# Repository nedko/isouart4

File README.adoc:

:notitle:
:keywords: isouart4
:docinfo: private-head,private-header

= isouart4 - Galvanically Isolated USB attached Quad UART

isouart4 - OSHW Galvanically Isolated USB attached Quad UART

.WORK IN PROGRESS
[NOTE]
This is Work In Progress.

link:bom/ibom.html[BOM - Bill Of Materials]

link:isouart4_sch.pdf[Schematic PDF]

link:https://gitea.ladish.org/nedko/isouart4[Project files] for link:https://kicad.org/[KiCAD]

image:isouart4-bottom.jpg[PCB bottom]

image:isouart4-top.jpg[PCB top]

== See also

 * link:https://github.com/hexeguitar/4WD_UART[4WD_UART by Piotr Zapart] is similar project that heavily influenced isouart4 design

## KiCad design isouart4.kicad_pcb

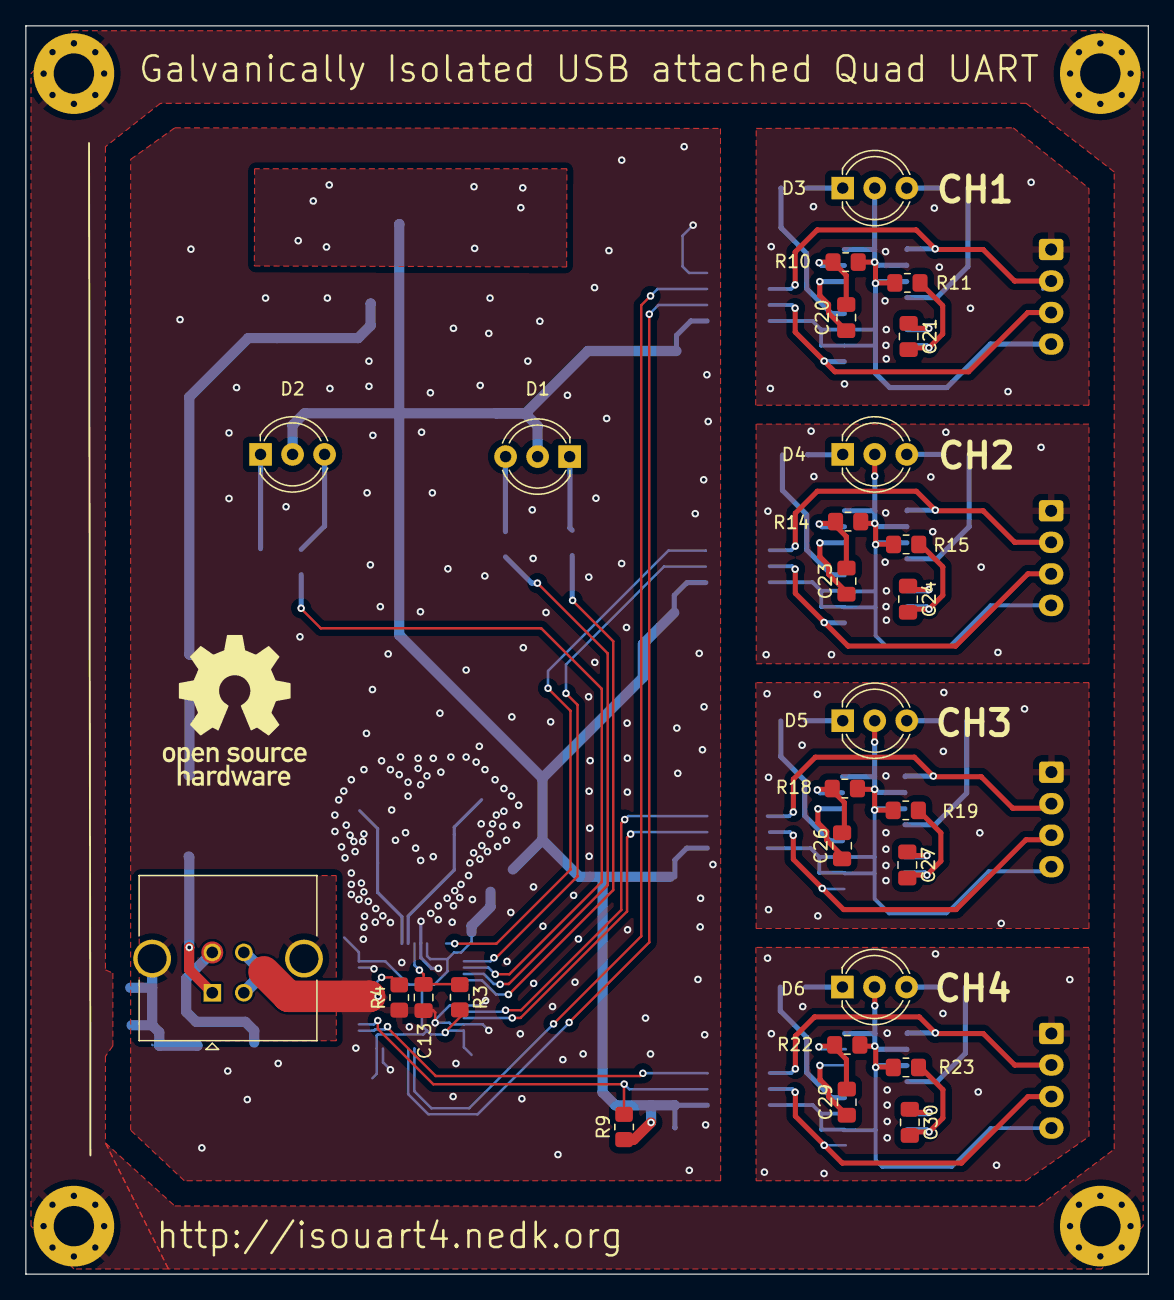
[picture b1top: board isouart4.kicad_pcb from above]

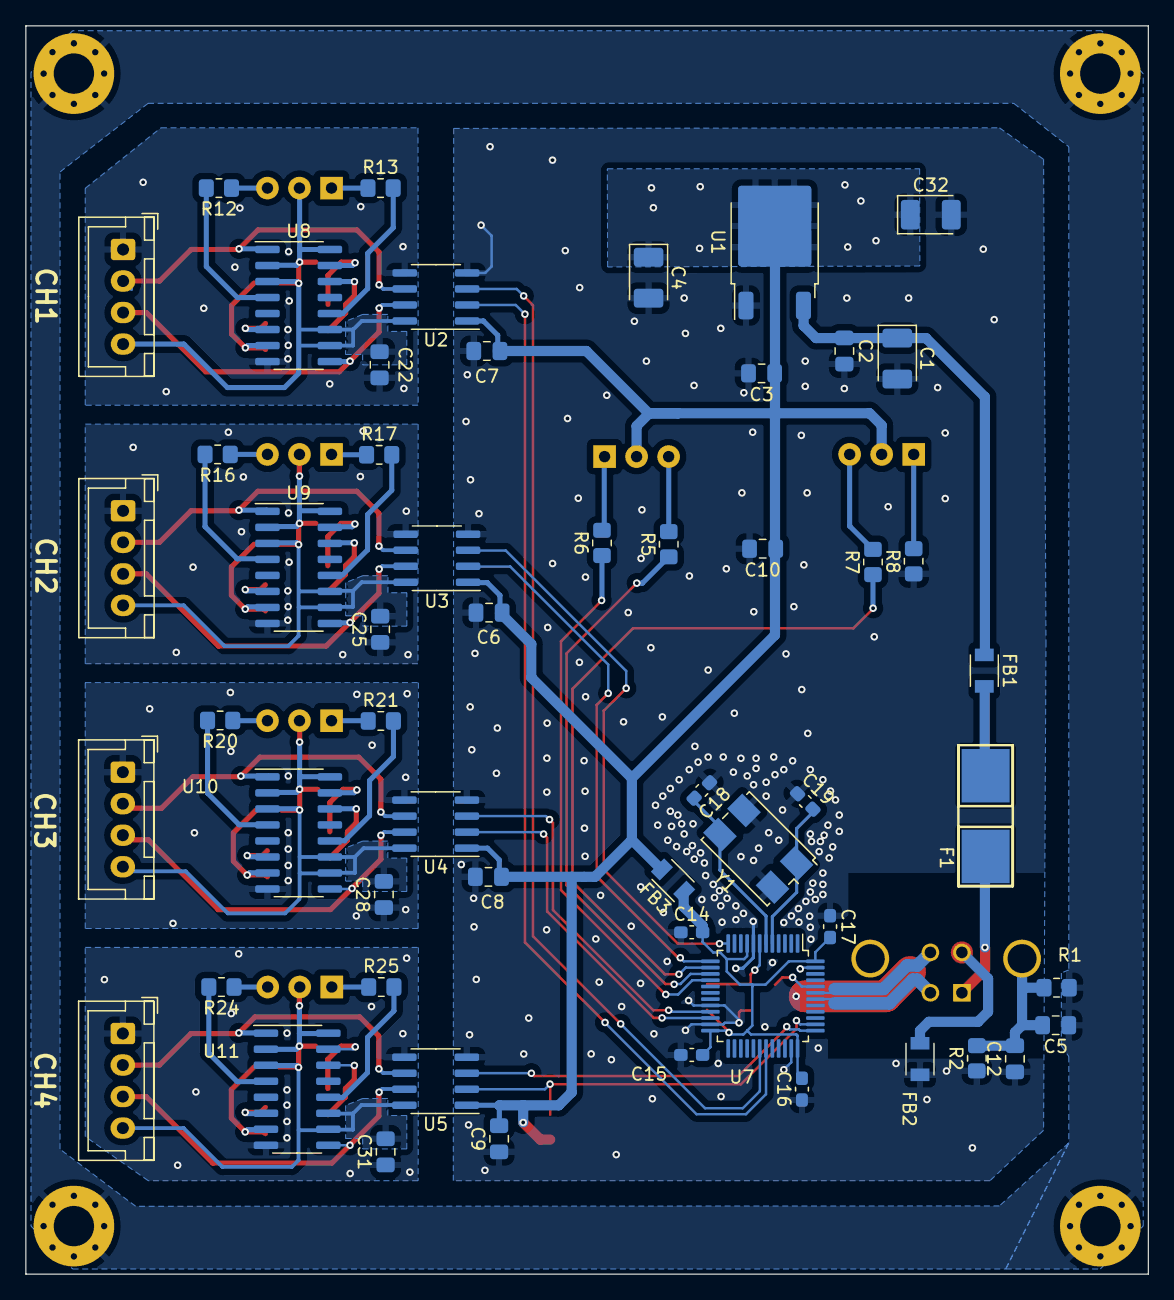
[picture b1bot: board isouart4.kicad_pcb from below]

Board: 2 copper layers, 89.0 x 99.0 mm, 87 parts (55 on the bottom side), 78 nets.

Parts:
C1, C4, C32: 2.2uF; CP_EIA-3528-15_AVX-H_Pad1.50x2.35mm_HandSolder
C2, C3, C6, C7, C8, C9, C10, C13, C22, C25, C28, C31: 100n; C_0805_2012Metric_Pad1.18x1.45mm_HandSolder
C5, C12: 4n7; C_0805_2012Metric_Pad1.18x1.45mm_HandSolder
C14, C15, C16, C17: 100n; C_0603_1608Metric_Pad1.08x0.95mm_HandSolder
C18, C19: 22p; C_0603_1608Metric_Pad1.08x0.95mm_HandSolder
C20, C21, C23, C24, C26, C27, C29, C30: 1uF; C_0805_2012Metric_Pad1.18x1.45mm_HandSolder
D1, D2, D3, D4, D5, D6: LED_Dual_KAK; LED_D5.0mm-3
F1: 100mA; FuseX
FB1, FB2, FB3: 100R; FB_0805_2012Metric
H1, H2, H3, H4: MountingHole; MountingHole_3.2mm_M3_Pad_Via
J1: USB_B; USB_B_TE_5787834_Vertical
J2, J3, J4, J5: Conn_01x04; JST_XH_B4B-XH-A_1x04_P2.50mm_Vertical
LOGO1: OSHW
R1: 4K7; R_0805_2012Metric_Pad1.20x1.40mm_HandSolder
R2: 1M; R_0805_2012Metric_Pad1.20x1.40mm_HandSolder
R3, R4, R9: 4k7; R_0805_2012Metric_Pad1.20x1.40mm_HandSolder
R5, R6, R7, R8, R12, R13, R16, R17, R20, R21, R24, R25: 1k; R_0805_2012Metric_Pad1.20x1.40mm_HandSolder
R10, R11, R14, R15, R18, R19, R22, R23: 220k; R_0805_2012Metric_Pad1.20x1.40mm_HandSolder
U1: LP2950CDT-3.3; TO-252-2
U2, U3, U4, U5: π122U31; SOIC-8_3.9x4.9mm_P1.27mm
U7: CH344Q; LQFP-48_7x7mm_P0.5mm
U8, U9, U10, U11: 74HC123; SOIC-16_3.9x9.9mm_P1.27mm
Y1: 8MHz; Crystal_SMD_7050-4Pin_7.0x5.0mm

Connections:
/GNDUSBCONN: FB2.1, J1.4 (GND)
/SHLD: C5.1, H1.1, H2.1, H3.1, H4.1, R1.1
/USB-UART4-CH344Q/ACT: R7.1, U7.14 (ACT|CFG|DCD3)
/USB-UART4-CH344Q/D+: J1.3 (D+), U7.43 (UD+)
/USB-UART4-CH344Q/D-: J1.2 (D-), U7.42 (UD-)
/USB-UART4-CH344Q/RESET: C13.2, R3.1, U7.7 (RESET)
/USB-UART4-CH344Q/RX1: U2.2 (VOA), U7.31 (RXD0)
/USB-UART4-CH344Q/RX2: U3.2 (VOA), U7.13 (RXD1)
/USB-UART4-CH344Q/RX3: U4.2 (VOA), U7.22 (RXD2)
/USB-UART4-CH344Q/RX4: R9.2, U5.2 (VOA), U7.38 (RXD3)
/USB-UART4-CH344Q/RX_S: R6.1, U7.16 (RX_S|DSR3)
/USB-UART4-CH344Q/TEST: R4.2, U7.44 (TEST)
/USB-UART4-CH344Q/TX1: U2.3 (VIB), U7.30 (TXD0)
/USB-UART4-CH344Q/TX2: U3.3 (VIB), U7.12 (TXD1)
/USB-UART4-CH344Q/TX3: U4.3 (VIB), U7.21 (TXD2)
/USB-UART4-CH344Q/TX4: U5.3 (VIB), U7.37 (TXD3)
/USB-UART4-CH344Q/TX_S: R5.1, U7.15 (TX_S|RI3)
/USB-UART4-CH344Q/VIN 3.3V: C3.1, C4.1, C6.2, C7.2, C8.2, C9.2, C10.1, C32.1, D1.2 (A), D2.2 (A), FB3.2, R9.1, U1.2 (VO), U2.1 (VDD1), U3.1 (VDD1), U4.1 (VDD1), U5.1 (VDD1)
/USB-UART4-CH344Q/XI: C19.2, U7.5 (XI), Y1.1
/USB-UART4-CH344Q/XO: C18.2, U7.6 (XO), Y1.3
/USBSHLD: C5.2, C12.2, J1.5 (Shield), R1.2, R2.2
/indicators-ch1/GNDMON: C22.1, J2.1, U2.5 (GND2), U8.8 (GND)
/indicators-ch1/RXMON: J2.3, U2.7 (VIA), U8.9 (A)
/indicators-ch1/TXMON: J2.2, U2.6 (VOB), U8.1 (A)
/indicators-ch1/V+MON: C22.2, D3.2 (A), J2.4, R10.1, R11.1, U2.8 (VDD2), U8.2 (B), U8.3 (Clr), U8.10 (B), U8.11 (Clr), U8.16 (VCC)
/indicators-ch2/GNDMON: C25.1, J3.1, U3.5 (GND2), U9.8 (GND)
/indicators-ch2/RXMON: J3.3, U3.7 (VIA), U9.9 (A)
/indicators-ch2/TXMON: J3.2, U3.6 (VOB), U9.1 (A)
/indicators-ch2/V+MON: C25.2, D4.2 (A), J3.4, R14.1, R15.1, U3.8 (VDD2), U9.2 (B), U9.3 (Clr), U9.10 (B), U9.11 (Clr), U9.16 (VCC)
/indicators-ch3/GNDMON: C28.1, J4.1, U4.5 (GND2), U10.8 (GND)
/indicators-ch3/RXMON: J4.3, U4.7 (VIA), U10.9 (A)
/indicators-ch3/TXMON: J4.2, U4.6 (VOB), U10.1 (A)
/indicators-ch3/V+MON: C28.2, D5.2 (A), J4.4, R18.1, R19.1, U4.8 (VDD2), U10.2 (B), U10.3 (Clr), U10.10 (B), U10.11 (Clr), U10.16 (VCC)
/indicators-ch4/GNDMON: C31.1, J5.1, U5.5 (GND2), U11.8 (GND)
/indicators-ch4/RXMON: J5.3, U5.7 (VIA), U11.9 (A)
/indicators-ch4/TXMON: J5.2, U5.6 (VOB), U11.1 (A)
/indicators-ch4/V+MON: C31.2, D6.2 (A), J5.4, R22.1, R23.1, U5.8 (VDD2), U11.2 (B), U11.3 (Clr), U11.10 (B), U11.11 (Clr), U11.16 (VCC)
GND: C1.2, C2.2, C3.2, C4.2, C6.1, C7.1, C8.1, C9.1, C10.2, C12.1, C13.1, C14.1, C15.1, C16.1, C17.1, C18.1, C19.1, C32.2, FB2.2, R2.1, R4.1, R8.1, U1.1 (GND), U2.4 (GND1), U3.4 (GND1), U4.4 (GND1), U5.4 (GND1), U7.8 (GND), U7.20 (GND), U7.23 (GND), U7.35 (GND), U7.47 (GND), Y1.2 (GND), Y1.4 (GND)
unnamed: C14.2, C15.2, C16.2, C17.2, FB3.1, R3.2, U7.9 (VCC), U7.24 (VCC), U7.36 (VCC), U7.48 (VCC)
unnamed: D1.1 (K1), R6.2
unnamed: D1.3 (K2), R5.2
unnamed: D2.1 (K1), R8.2
unnamed: D2.3 (K2), R7.2
unnamed: D3.1 (K1), R13.1
unnamed: D3.3 (K2), R12.1
unnamed: D4.1 (K1), R17.1
unnamed: D4.3 (K2), R16.1
unnamed: D5.1 (K1), R21.1
unnamed: D5.3 (K2), R20.1
unnamed: D6.1 (K1), R25.1
unnamed: D6.3 (K2), R24.1
unnamed: F1.2, FB1.2
unnamed: F1.1, J1.1 (VBUS)
unnamed: C1.1, C2.1, FB1.1, U1.3 (VI)
unnamed: C20.1, U8.14 (Cext)
unnamed: C20.2, R10.2, U8.15 (RCext)
unnamed: R12.2, U8.4 (~Q)
unnamed: C21.1, U8.6 (Cext)
unnamed: C21.2, R11.2, U8.7 (RCext)
unnamed: R13.2, U8.12 (~Q)
unnamed: C23.1, U9.14 (Cext)
unnamed: C23.2, R14.2, U9.15 (RCext)
unnamed: R16.2, U9.4 (~Q)
unnamed: C24.1, U9.6 (Cext)
unnamed: C24.2, R15.2, U9.7 (RCext)
unnamed: R17.2, U9.12 (~Q)
unnamed: C26.1, U10.14 (Cext)
unnamed: C26.2, R18.2, U10.15 (RCext)
unnamed: R20.2, U10.4 (~Q)
unnamed: C27.1, U10.6 (Cext)
unnamed: C27.2, R19.2, U10.7 (RCext)
unnamed: R21.2, U10.12 (~Q)
unnamed: C29.1, U11.14 (Cext)
unnamed: C29.2, R22.2, U11.15 (RCext)
unnamed: R24.2, U11.4 (~Q)
unnamed: C30.1, U11.6 (Cext)
unnamed: C30.2, R23.2, U11.7 (RCext)
unnamed: R25.2, U11.12 (~Q)

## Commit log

2023-09-21 Initial draft of isouart4
2023-09-22 Flush
2023-09-28 switch to CH344Q
2023-10-04 More feng shui
2023-10-07 pcb-route all uart channels
2023-12-06 Flush latest changes
2023-12-06 current website
2023-12-06 generate website from adoc
2023-12-07 Update pcb raytraced renderings
2023-12-07 website: Update ibom
2023-12-07 remove problematic vias
2023-12-07 Add π122U31 to the project lib
2023-12-07 H_passives:CAP_NP -> isouart4:CAP_NP
2023-12-07 Use the custom isouart4:Crystal_Small instead of Device:Crystal_Small
2023-12-07 remove X1
2023-12-07 Restore 0805 capacitor footprints; Use anotherguse/FuseX copy form isouart4 lib
2023-12-07 add files for project lib tables; add FuseX too isouart4.pretty
2023-12-07 adjust plygon of isobarier keepout
2023-12-07 Update ibom
2023-12-07 remove unused kicad_sch files
2023-12-07 .gitignore generated and kicad lock files
2023-12-07 switch C28-C33 to 0603
2023-12-07 reannotate
2023-12-07 Update pcb raytrace renders
2023-12-07 Fix ferrite bead 3D model paths
2023-12-07 Add 3D model for the 7050 xtal
    https://grabcad.com/library/crystal-smd-7050-4pin-7-0x5-0mm-1
2023-12-07 Re-raytrace after 3D models setup
2023-12-07 Crop the bottom side raytrace
2023-12-10 Nonfunctional changes to schematic (positions)
2023-12-10 Fix xtal 7050 footprint warning by creating isouart4 footprint copy
2023-12-10 Fix FB footprint warning by creating isouart4 footprint copy
2023-12-10 Fix Reference fields
2023-12-10 Add fuse footpront courtyard; TH->SMD
2023-12-10 Unignore all currently ignored pcb tests
2023-12-10 Adjust R1, C1 and C10 poisitions
2023-12-10 pcb: adjust mounting hole positions; SHLD outer line at 0.4mm from edge
2023-12-11 adjust power filtering
2023-12-12 AMS1117-3.3 -> LP2950CDT-3.3 (reduce usb downstream capacitance)
2023-12-12 adjust silkscreen and led positions; reannotate
2023-12-12 Add OSHW logo
2023-12-12 website: update pcb raytrace exports
2023-12-12 website: Add isouart4_sch.pdf
2023-12-12 website: regenerate from source
2023-12-12 README.adoc: Add a newline
2023-12-12 add kicad 3d view "E"
2023-12-12 website: Update pcb raytrace renders (crop)
2023-12-12 website: Use jpeg instead of png
2023-12-12 Switch main sheet of schematic from A3 to A4
2023-12-12 Add some title text to the schematic sheets
2023-12-12 Update website/isouart4_sch.pdf (A4, more text)
2023-12-12 Adjust OSHW logo to have footprint and use it
2023-12-13 Link 4WD_UART by @hexeguitar in the README
2023-12-13 Update website/isouart4_sch.pdf (kicad default colour style)
2023-12-13 isouart4.pretty/OSHW.kicad_mod: set exclude_from_bom allow_missing_courtyard
2023-12-13 increase via size to 0.6mm and via annular width to 0.13mm
2023-12-14 adjust regulator tantalum capacitors (1+3.3uF -> 3x2.2uF)
2023-12-15 rework ESD protection (handsolder sot-23 on USB connector)
2023-12-15 fix ESD protection wiring (now both D+ and D-)
2023-12-21 website: update schematic pdf and pcb raytrace exports
2023-12-21 website: update pcb raytrace exports (jpg)
2023-12-21 website: hyperlink kicad.org
